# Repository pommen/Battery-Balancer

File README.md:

# Battery-Balancer
Cecking and discharing batteries until they are all the same voltage (cap)

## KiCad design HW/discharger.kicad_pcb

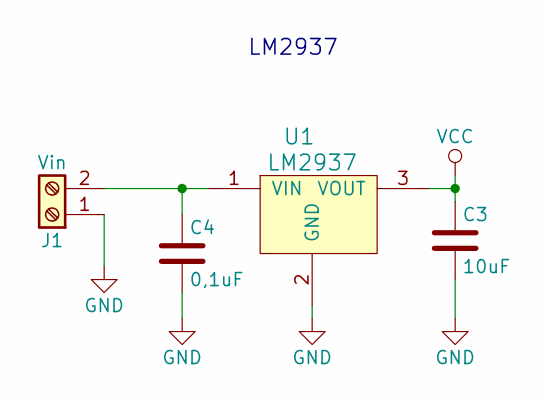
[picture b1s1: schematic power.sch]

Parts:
C3: 10uF; C_0805_HandSoldering
C4: 0,1uF; C_0805_HandSoldering
J1: Vin; TerminalBlock_bornier-2_P5.08mm
U1: LM2937; SOT-223-3_TabPin2

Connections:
GND: C3.2, C4.2, J1.1, U1.2 (GND); also elsewhere on the board
unnamed: C4.1, J1.2, U1.1 (VIN)
VCC: C3.1, U1.3 (VOUT); also elsewhere on the board

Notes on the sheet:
LM2937

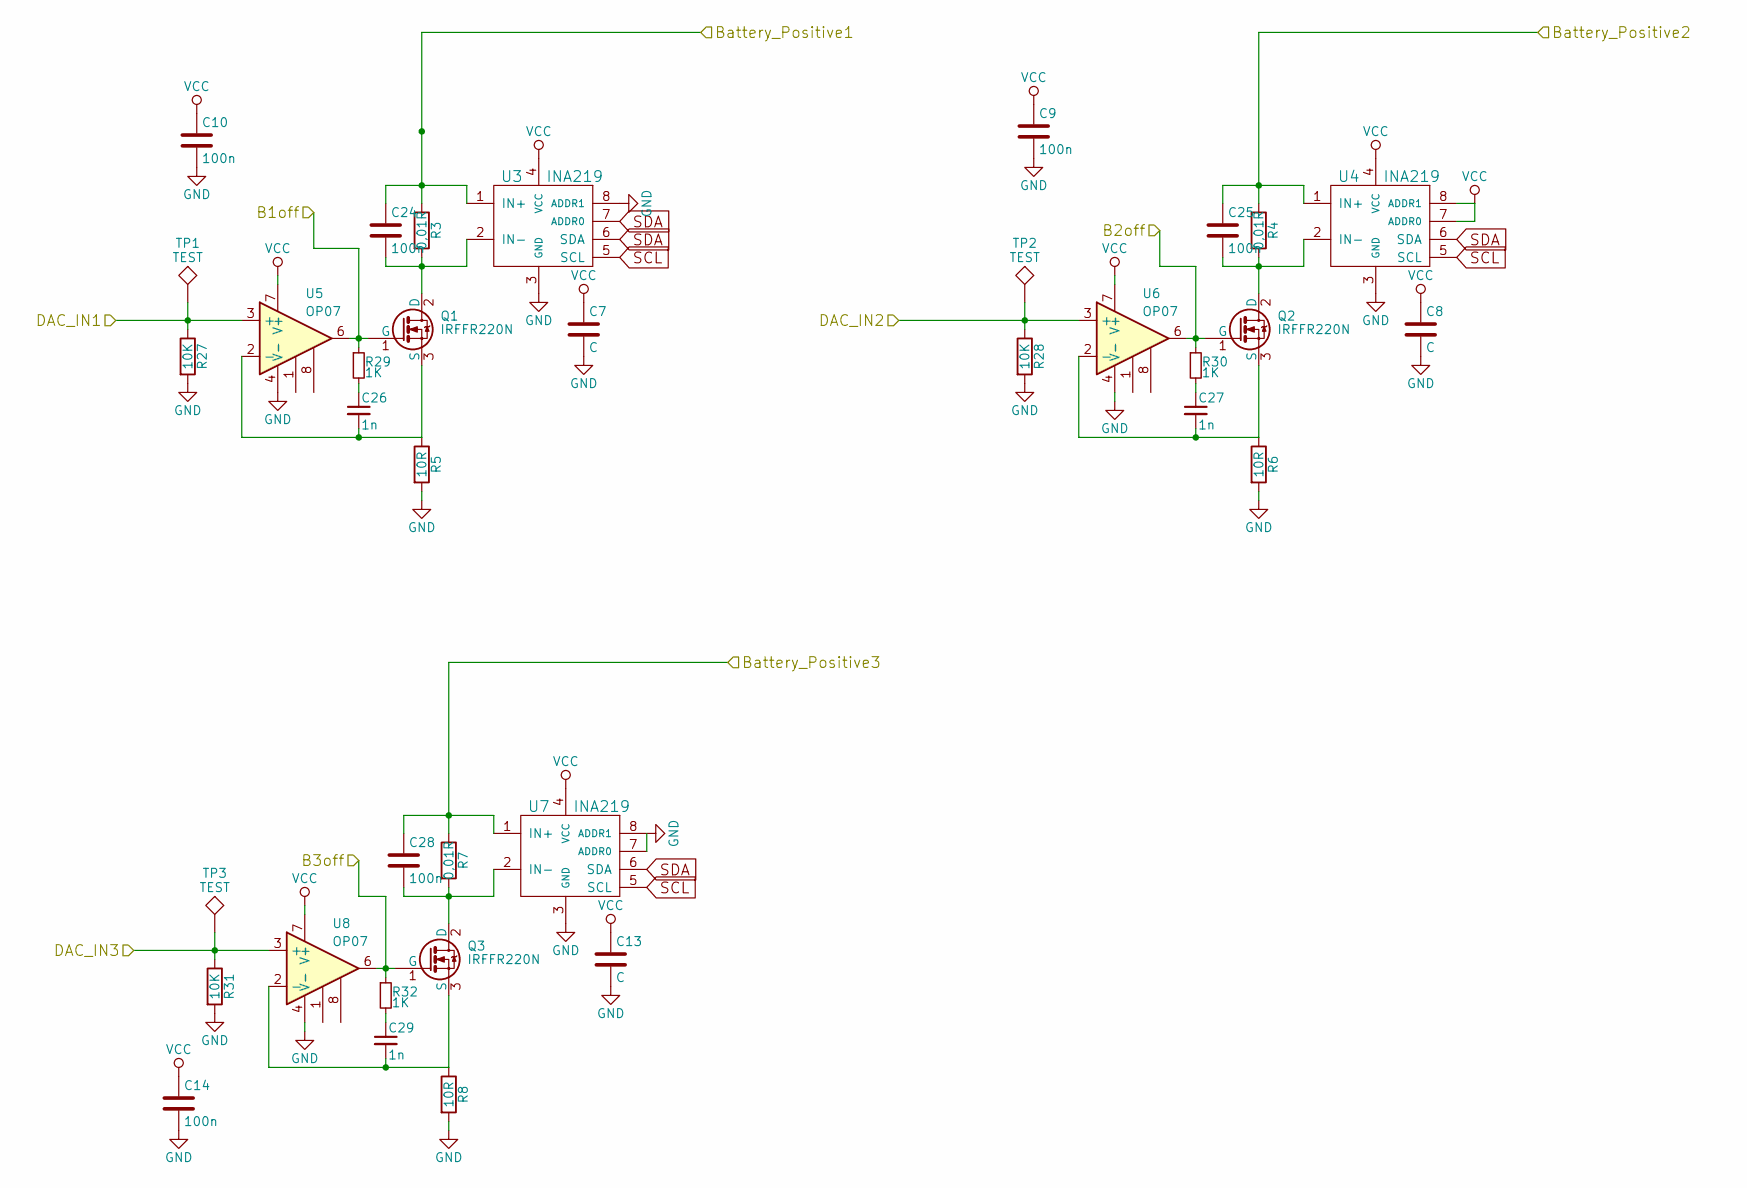
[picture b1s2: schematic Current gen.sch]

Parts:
C7, C8, C13: C; C_0805_HandSoldering
C9, C10, C14, C24, C25, C28: 100n; C_0805_HandSoldering
C26, C27, C29: 1n; C_0805_HandSoldering
Q1, Q2, Q3: IRFFR220N; TO-252-2
R3, R4, R7: 0,01R; R_2512_HandSoldering
R5, R6, R8: 10R; R_2512_HandSoldering
R27, R28, R31: 10K; R_0805_HandSoldering
R29, R30, R32: 1K; R_0805_HandSoldering
TP1, TP2, TP3: TEST; Pin_Header_Straight_1x01_Pitch2.54mm
U3, U4, U7: INA219; SOT-23-8_Handsoldering
U5, U6, U8: OP07; DIP-8_W7.62mm_Socket_LongPads

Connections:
/Battery connections/BatteryPositive1: C24.1, R3.1, U3.1 (IN+); also elsewhere on the board
/Battery connections/BatteryPositive2: C25.1, R4.1, U4.1 (IN+); also elsewhere on the board
/Battery connections/BatteryPositive3: C28.1, R7.1, U7.1 (IN+); also elsewhere on the board
/Dynamic load/B1off: Q1.1 (G), R29.1, U5.6; also elsewhere on the board
/Dynamic load/B2off: Q2.1 (G), R30.1, U6.6; also elsewhere on the board
/Dynamic load/B3off: Q3.1 (G), R32.1, U8.6; also elsewhere on the board
/Dynamic load/DAC_IN1: R27.1, TP1.1, U5.3 (+); also elsewhere on the board
/Dynamic load/DAC_IN2: R28.1, TP2.1, U6.3 (+); also elsewhere on the board
/Dynamic load/DAC_IN3: R31.1, TP3.1, U8.3 (+); also elsewhere on the board
GND: C7.2, C8.2, C9.2, C10.2, C13.2, C14.2, R5.2, R6.2, R8.2, R27.2, R28.2, R31.2, U3.3 (GND), U3.8 (ADDR1), U4.3 (GND), U5.4 (V-), U6.4 (V-), U7.3 (GND), U7.7 (ADDR0), U7.8 (ADDR1), U8.4 (V-); also elsewhere on the board
unnamed: C24.2, Q1.2 (D), R3.2, U3.2 (IN-)
unnamed: C25.2, Q2.2 (D), R4.2, U4.2 (IN-)
unnamed: C26.1, R29.2
unnamed: C26.2, Q1.3 (S), R5.1, U5.2 (-)
unnamed: C27.1, R30.2
unnamed: C27.2, Q2.3 (S), R6.1, U6.2 (-)
unnamed: C28.2, Q3.2 (D), R7.2, U7.2 (IN-)
unnamed: C29.1, R32.2
unnamed: C29.2, Q3.3 (S), R8.1, U8.2 (-)
SCL: U3.5 (SCL), U4.5 (SCL), U7.5 (SCL); also elsewhere on the board
SDA: U3.6 (SDA), U3.7 (ADDR0), U4.6 (SDA), U7.6 (SDA); also elsewhere on the board
VCC: C7.1, C8.1, C9.1, C10.1, C13.1, C14.1, U3.4 (VCC), U4.4 (VCC), U4.7 (ADDR0), U4.8 (ADDR1), U5.7 (V+), U6.7 (V+), U7.4 (VCC), U8.7 (V+); also elsewhere on the board

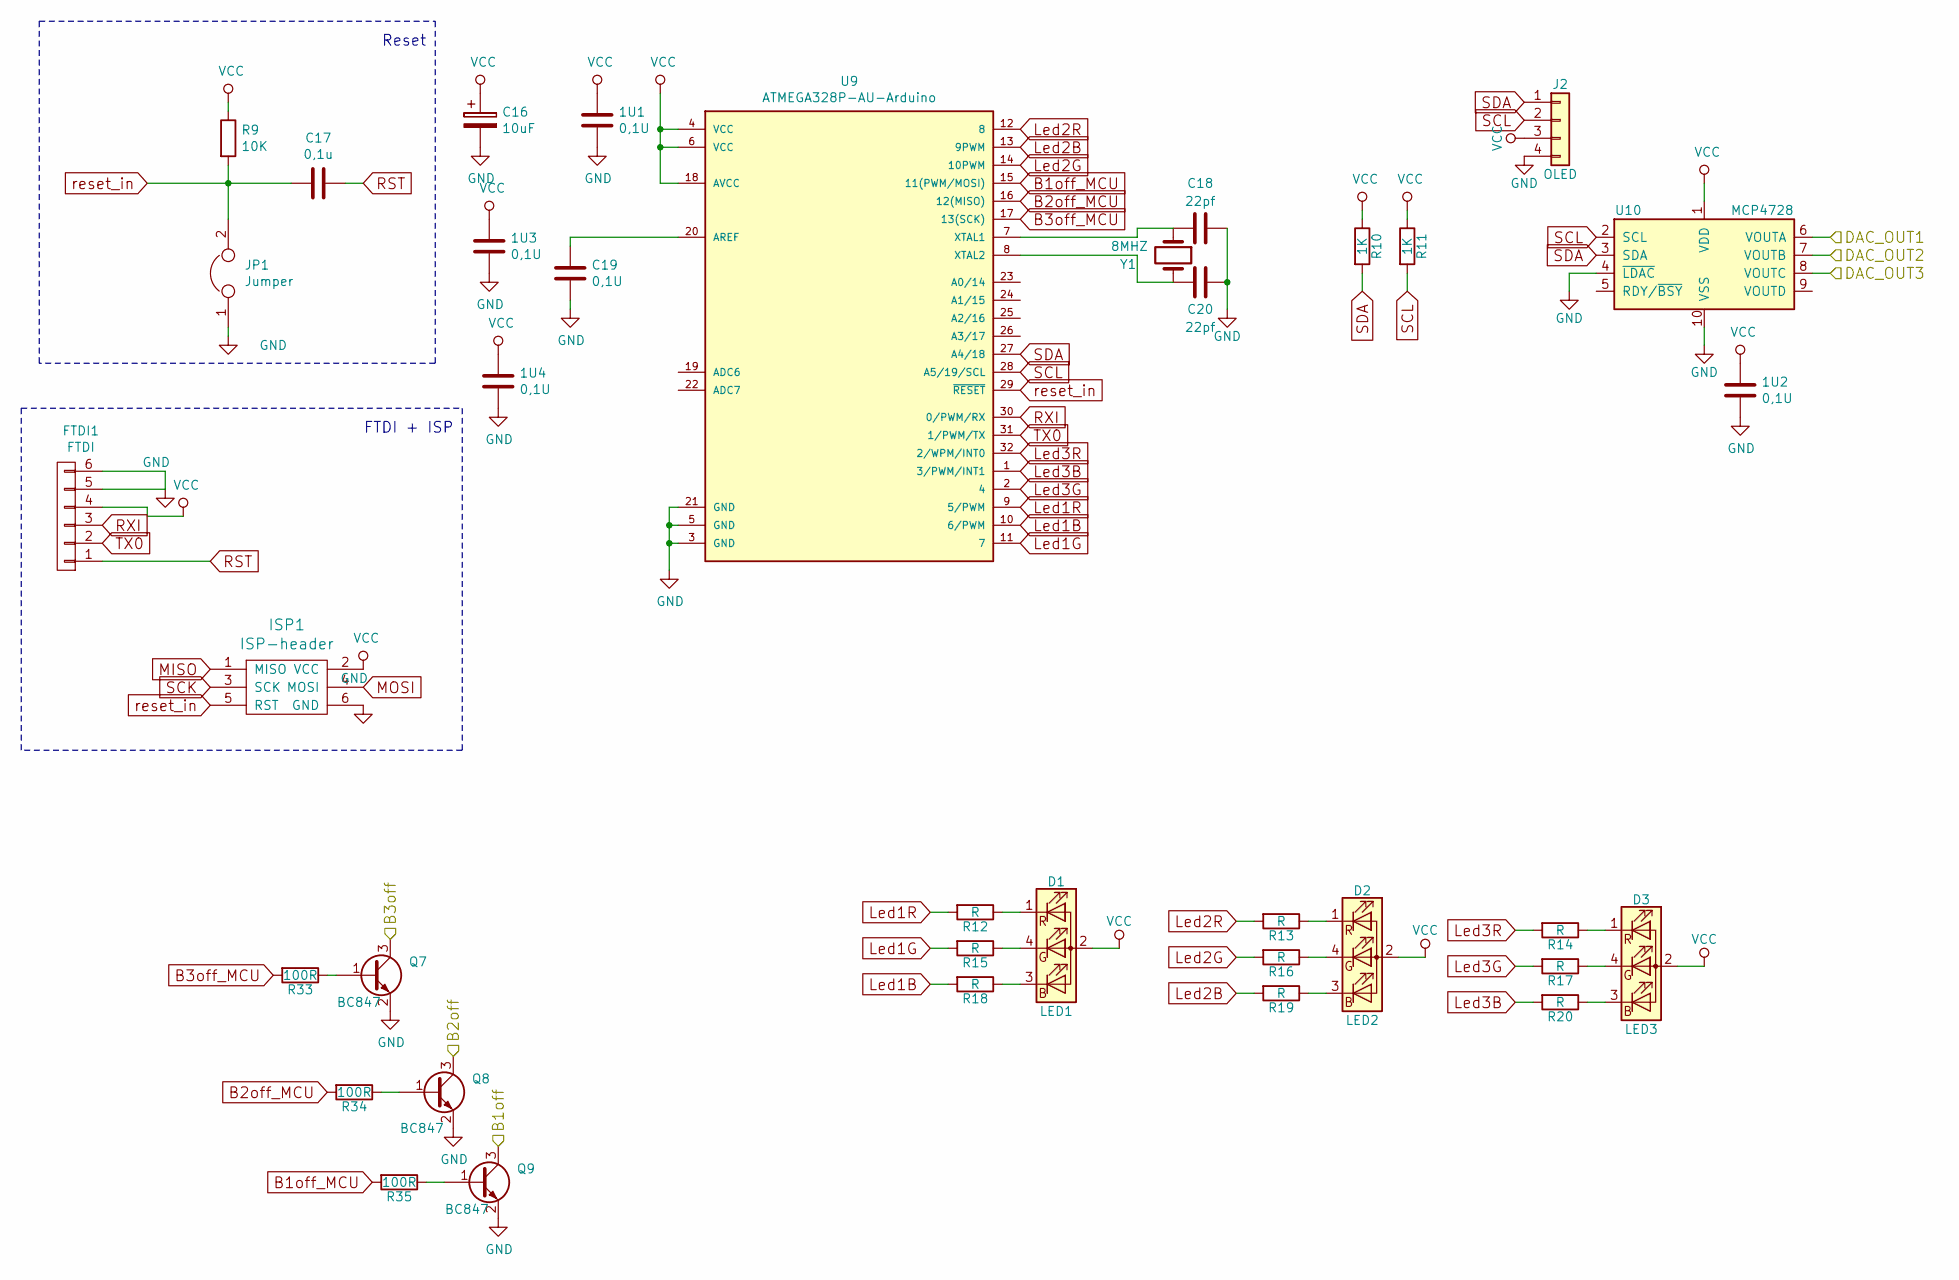
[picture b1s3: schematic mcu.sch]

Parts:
1U1, 1U2, 1U3, 1U4: 0,1U; C_0805_HandSoldering
C16: 10uF; CP_Tantalum_Case-C_EIA-6032-28_Hand
C17: 0,1u; C_0805_HandSoldering
C18, C20: 22pf; C_0805_HandSoldering
C19: 0,1U; C_0805_HandSoldering
D1: LED1; LED_D5.0mm-4
D2: LED2; LED_D5.0mm-4
D3: LED3; LED_D5.0mm-4
FTDI1: FTDI; Pin_Header_Straight_1x06_Pitch2.54mm
ISP1: ISP-header; Pin_Header_Straight_2x03_Pitch2.54mm
J2: OLED; Pin_Header_Straight_1x04_Pitch2.54mm
JP1: Jumper; Pin_Header_Straight_1x03_Pitch2.54mm
Q7, Q8, Q9: BC847; SOT-23_Handsoldering
R9: 10K; R_0805_HandSoldering
R10, R11: 1K; R_0805_HandSoldering
R12, R13, R14, R15, R16, R17, R18, R19, R20: R; R_0805_HandSoldering
R33, R34, R35: 100R; R_0805_HandSoldering
U9: ATMEGA328P-AU-Arduino; TQFP-32_7x7mm_Pitch0.8mm
U10: MCP4728; DIP-10_W7.62mm_LongPads
Y1: 8MHZ; Crystal_HC18-U_Vertical

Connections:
/Dynamic load/B1off: Q9.3 (C); also elsewhere on the board
/Dynamic load/B2off: Q8.3 (C); also elsewhere on the board
/Dynamic load/B3off: Q7.3 (C); also elsewhere on the board
/Dynamic load/DAC_IN1: U10.6 (VOUTA); also elsewhere on the board
/Dynamic load/DAC_IN2: U10.7 (VOUTB); also elsewhere on the board
/Dynamic load/DAC_IN3: U10.8 (VOUTC); also elsewhere on the board
B1off_MCU: R35.2, U9.15 (11(PWM/MOSI))
B2off_MCU: R34.2, U9.16 (12(MISO))
B3off_MCU: R33.2, U9.17 (13(SCK))
GND: 1U1.2, 1U2.2, 1U3.2, 1U4.2, C16.2, C18.1, C19.2, C20.1, FTDI1.5, FTDI1.6, ISP1.6 (GND), J2.4, JP1.1, Q7.2 (E), Q8.2 (E), Q9.2 (E), U9.3 (GND), U9.5 (GND), U9.21 (GND), U10.4 (~LDAC), U10.10 (VSS); also elsewhere on the board
Led1B: R18.2, U9.10 (6/PWM)
Led1G: R15.2, U9.11 (7)
Led1R: R12.2, U9.9 (5/PWM)
Led2B: R19.2, U9.13 (9PWM)
Led2G: R16.2, U9.14 (10PWM)
Led2R: R13.2, U9.12 (8)
Led3B: R20.2, U9.1 (3/PWM/INT1)
Led3G: R17.2, U9.2 (4)
Led3R: R14.2, U9.32 (2/WPM/INT0)
unnamed: C18.2, U9.7 (XTAL1), Y1.1
unnamed: C19.1, U9.20 (AREF)
unnamed: C20.2, U9.8 (XTAL2), Y1.2
unnamed: D1.1 (RK), R12.1
unnamed: D1.3 (BK), R18.1
unnamed: D1.4 (GK), R15.1
unnamed: D2.1 (RK), R13.1
unnamed: D2.3 (BK), R19.1
unnamed: D2.4 (GK), R16.1
unnamed: D3.1 (RK), R14.1
unnamed: D3.3 (BK), R20.1
unnamed: D3.4 (GK), R17.1
unnamed: Q7.1 (B), R33.1
unnamed: Q8.1 (B), R34.1
unnamed: Q9.1 (B), R35.1
RST: C17.1, FTDI1.1
RXI: FTDI1.3, U9.30 (0/PWM/RX)
SCL: J2.2, R11.2, U9.28 (A5/19/SCL), U10.2 (SCL); also elsewhere on the board
SDA: J2.1, R10.2, U9.27 (A4/18), U10.3 (SDA); also elsewhere on the board
TX0: FTDI1.2, U9.31 (1/PWM/TX)
VCC: 1U1.1, 1U2.1, 1U3.1, 1U4.1, C16.1, D1.2 (A), D2.2 (A), D3.2 (A), FTDI1.4, ISP1.2 (VCC), J2.3, R9.1, R10.1, R11.1, U9.4 (VCC), U9.6 (VCC), U9.18 (AVCC), U10.1 (VDD); also elsewhere on the board
reset_in: C17.2, ISP1.5 (RST), JP1.2, R9.2, U9.29 (~RESET~)

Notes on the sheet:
FTDI + ISP
Reset

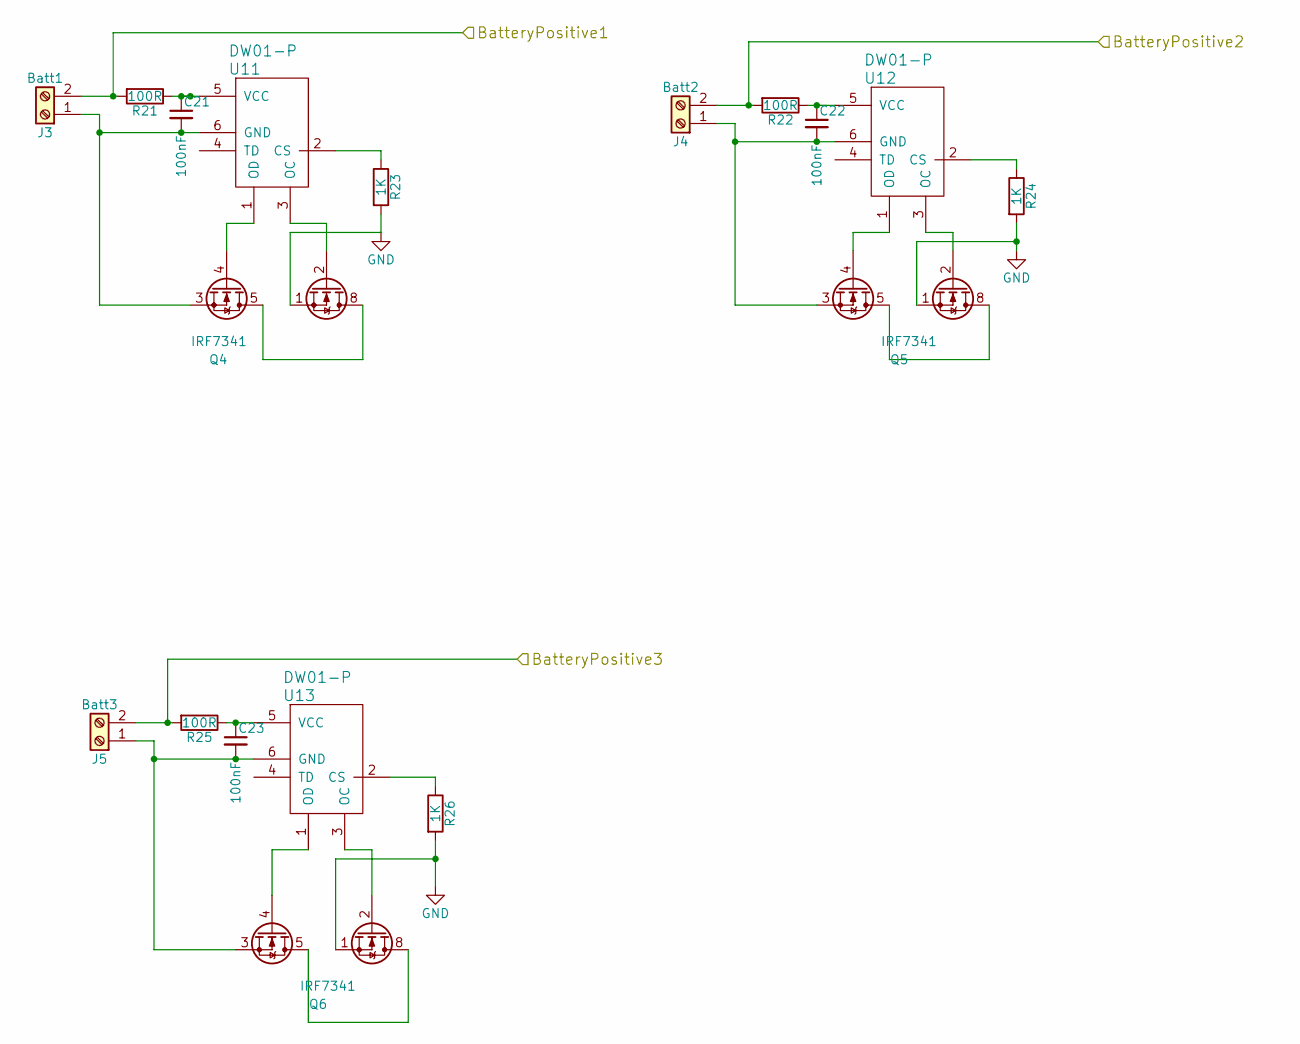
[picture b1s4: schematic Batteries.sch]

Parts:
C21, C22, C23: 100nF; C_0805_HandSoldering
J3: Batt1; TerminalBlock_bornier-2_P5.08mm
J4: Batt2; TerminalBlock_bornier-2_P5.08mm
J5: Batt3; TerminalBlock_bornier-2_P5.08mm
Q4, Q5, Q6: IRF7341; SO-8_5.3x6.2mm_Pitch1.27mm
R21, R22, R25: 100R; R_0805_HandSoldering
R23, R24, R26: 1K; R_0805_HandSoldering
U11, U12, U13: DW01-P; SOT-23-6_Handsoldering

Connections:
/Battery connections/BatteryPositive1: J3.2, R21.2; also elsewhere on the board
/Battery connections/BatteryPositive2: J4.2, R22.2; also elsewhere on the board
/Battery connections/BatteryPositive3: J5.2, R25.2; also elsewhere on the board
GND: Q4.1 (S1), Q5.1 (S1), Q6.1 (S1), R23.2, R24.2, R26.2; also elsewhere on the board
unnamed: C21.1, R21.1, U11.5 (VCC)
unnamed: C21.2, J3.1, Q4.3 (S2), U11.6 (GND)
unnamed: C22.1, R22.1, U12.5 (VCC)
unnamed: C22.2, J4.1, Q5.3 (S2), U12.6 (GND)
unnamed: C23.1, R25.1, U13.5 (VCC)
unnamed: C23.2, J5.1, Q6.3 (S2), U13.6 (GND)
unnamed: Q4.2 (G1), U11.3 (OC)
unnamed: Q4.4 (G2), U11.1 (OD)
unnamed: Q4.5 (D2), Q4.8 (D1)
unnamed: Q5.2 (G1), U12.3 (OC)
unnamed: Q5.4 (G2), U12.1 (OD)
unnamed: Q5.5 (D2), Q5.8 (D1)
unnamed: Q6.2 (G1), U13.3 (OC)
unnamed: Q6.4 (G2), U13.1 (OD)
unnamed: Q6.5 (D2), Q6.8 (D1)
unnamed: R23.1, U11.2 (CS)
unnamed: R24.1, U12.2 (CS)
unnamed: R26.1, U13.2 (CS)

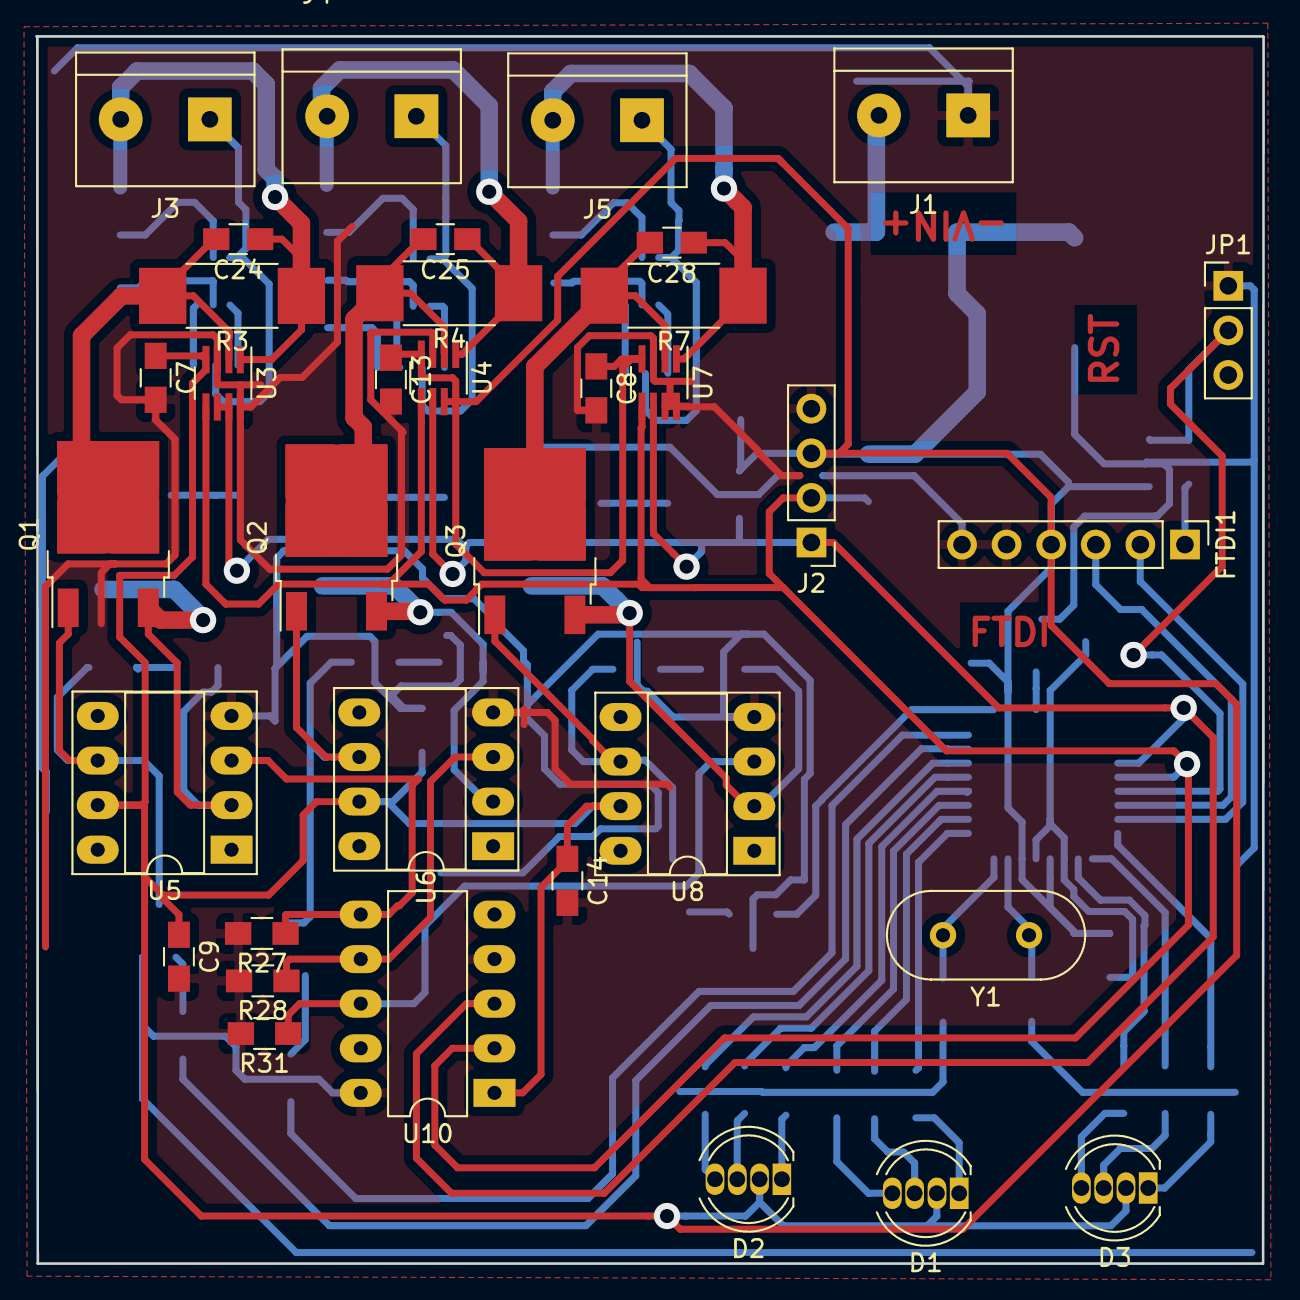
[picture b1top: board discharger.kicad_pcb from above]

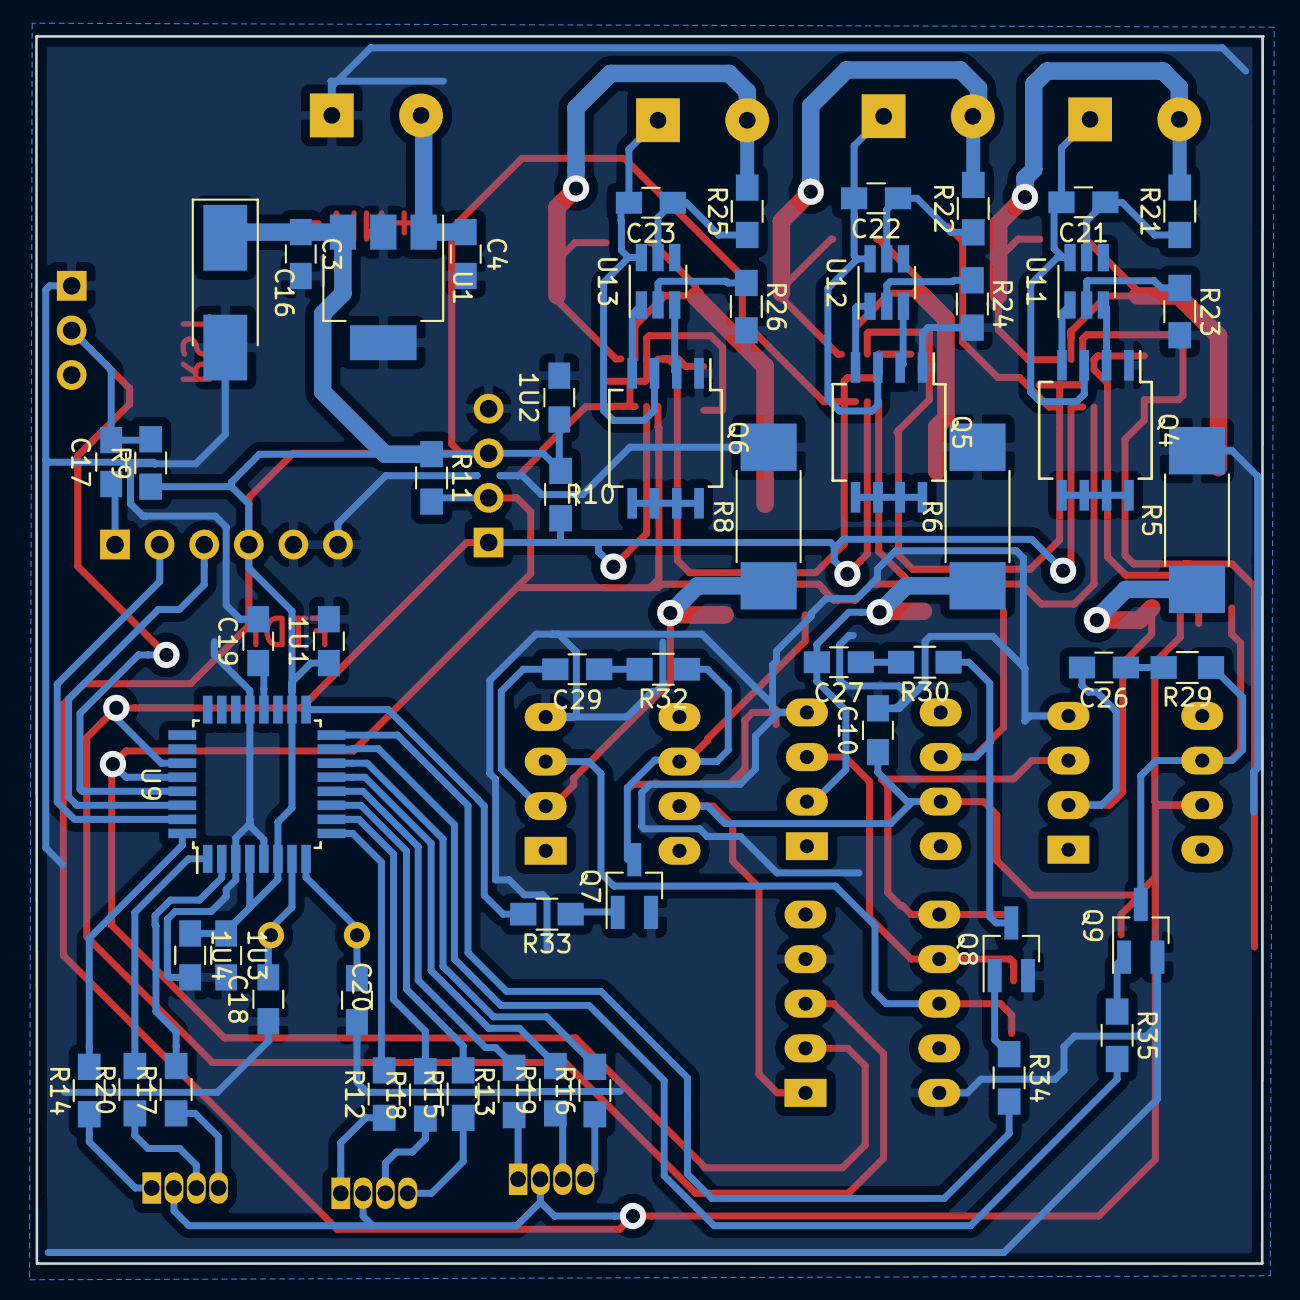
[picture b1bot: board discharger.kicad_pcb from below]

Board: 2 copper layers, 69.9 x 69.9 mm, 91 parts (56 on the bottom side), 72 nets.

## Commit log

2018-03-14 Less bad
2018-03-14 SMD crystal
2018-03-19 grbl
2018-04-23 better layout
2018-04-24 Layout complete
    Done
